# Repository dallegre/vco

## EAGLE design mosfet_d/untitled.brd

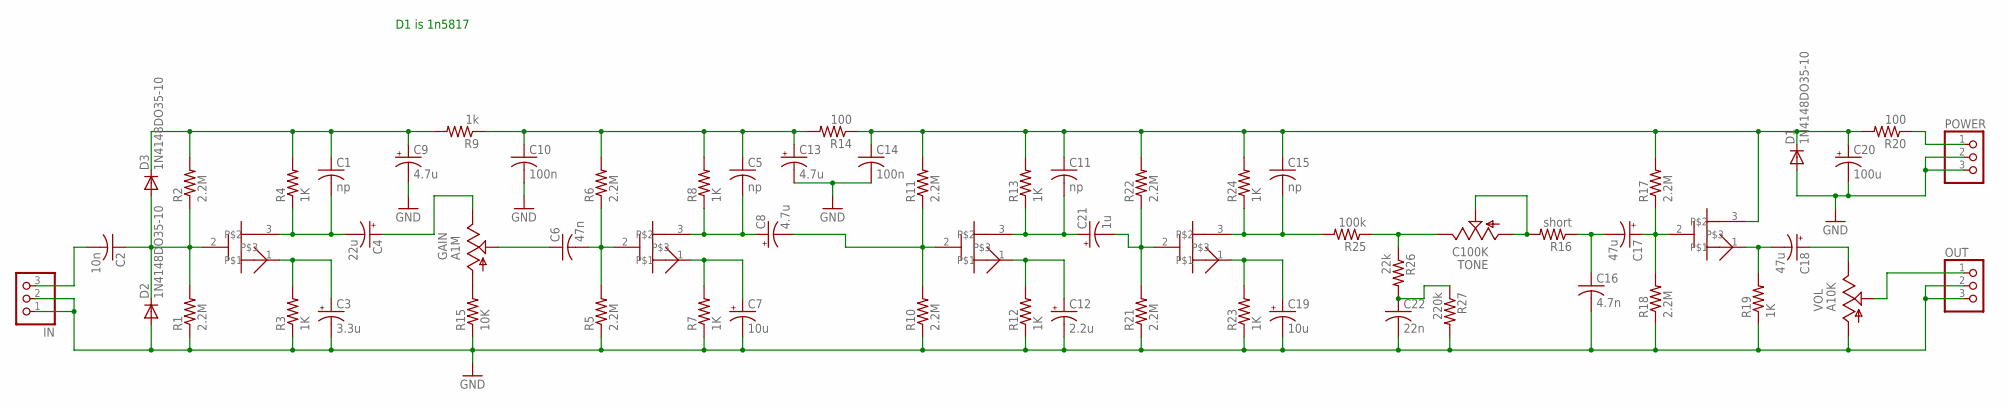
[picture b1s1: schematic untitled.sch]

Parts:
C1, C5, C11, C15: np; C050-030X075
C2: 10n; C050-030X075
C3: 3.3u; E2-5
C4: 22u; E2-5
C6: 47n; C050-030X075
C7, C19: 10u; E2-5
C8, C9, C13: 4.7u; E2-5
C10, C14: 100n; C050-030X075
C12: 2.2u; E2-5
C16: 4.7n; C050-030X075
C17, C18: 47u; E2-5
C20: 100u; E2-5
C21: 1u; E2-5
C22: 22n; C050-030X075
D1, D2, D3: 1N4148DO35-10; DO35-10
GAIN: A1M; 3RP/1610N
IN: PINHD-1X3; 1X03
OUT: PINHD-1X3; 1X03
POWER: PINHD-1X3; 1X03
R1, R2, R5, R6, R10, R11, R17, R18, R21, R22: 2.2M; 0207/7
R3, R4, R7, R8, R12, R13, R19, R23, R24: 1K; 0207/7
R9: 1k; 0207/7
R14, R20: 100; 0207/7
R15: 10K; 0207/7
R16: short; 0207/7
R25: 100k; 0207/7
R26: 22k; 0207/7
R27: 220k; 0207/7
TONE: C100K; 3RP/1610N
U$1, U$2, U$3, U$4, U$5: 2N7000_2; TO92
VOL: A10K; 3RP/1610N

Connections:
GND: C3.-, C7.-, C9.-, C10.2, C12.-, C13.-, C14.2, C16.2, C19.-, C20.-, C22.2, D1.A, D2.A, IN.1, IN.2, OUT.2, OUT.3, POWER.2, POWER.3, R1.1, R3.1, R5.1, R7.1, R10.1, R12.1, R15.1, R18.1, R19.1, R21.1, R23.1, R27.2, VOL.3 (A)
unnamed: C2.1, D2.C, D3.A, R1.2, R2.1, U$1.2
unnamed: C1.2, C4.-, R4.1, U$1.3
unnamed: C1.1, C9.+, D3.C, R2.2, R4.2, R9.2
unnamed: C4.+, GAIN.1 (E)
unnamed: C3.+, R3.2, U$1.1
unnamed: C6.2, R5.2, R6.1, U$2.2
unnamed: C5.2, C8.+, R8.1, U$2.3
unnamed: C2.2, IN.3
unnamed: C7.+, R7.2, U$2.1
unnamed: C16.1, C17.-, R16.1
unnamed: C6.1, GAIN.2 (S)
unnamed: C11.2, C21.+, R13.1, U$3.3
unnamed: C5.1, C10.1, C13.+, R6.2, R8.2, R9.1, R14.2
unnamed: C12.+, R12.2, U$3.1
unnamed: C8.-, R10.2, R11.1, U$3.2
unnamed: GAIN.3 (A), R15.2
unnamed: POWER.1, R20.1
unnamed: C17.+, R17.1, R18.2, U$4.2
unnamed: C11.1, C14.1, C15.1, C20.+, D1.C, R11.2, R13.2, R14.1, R17.2, R20.2, R22.2, R24.2, U$4.3
unnamed: R16.2, TONE.2 (S), TONE.3 (A)
unnamed: C18.-, R19.2, U$4.1
unnamed: C18.+, VOL.1 (E)
unnamed: C15.2, R24.1, R25.2, U$5.3
unnamed: OUT.1, VOL.2 (S)
unnamed: C19.+, R23.2, U$5.1
unnamed: C21.-, R21.2, R22.1, U$5.2
unnamed: C22.1, R26.2, R27.1
unnamed: R25.1, R26.1, TONE.1 (E)

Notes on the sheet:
D1 is 1n5817

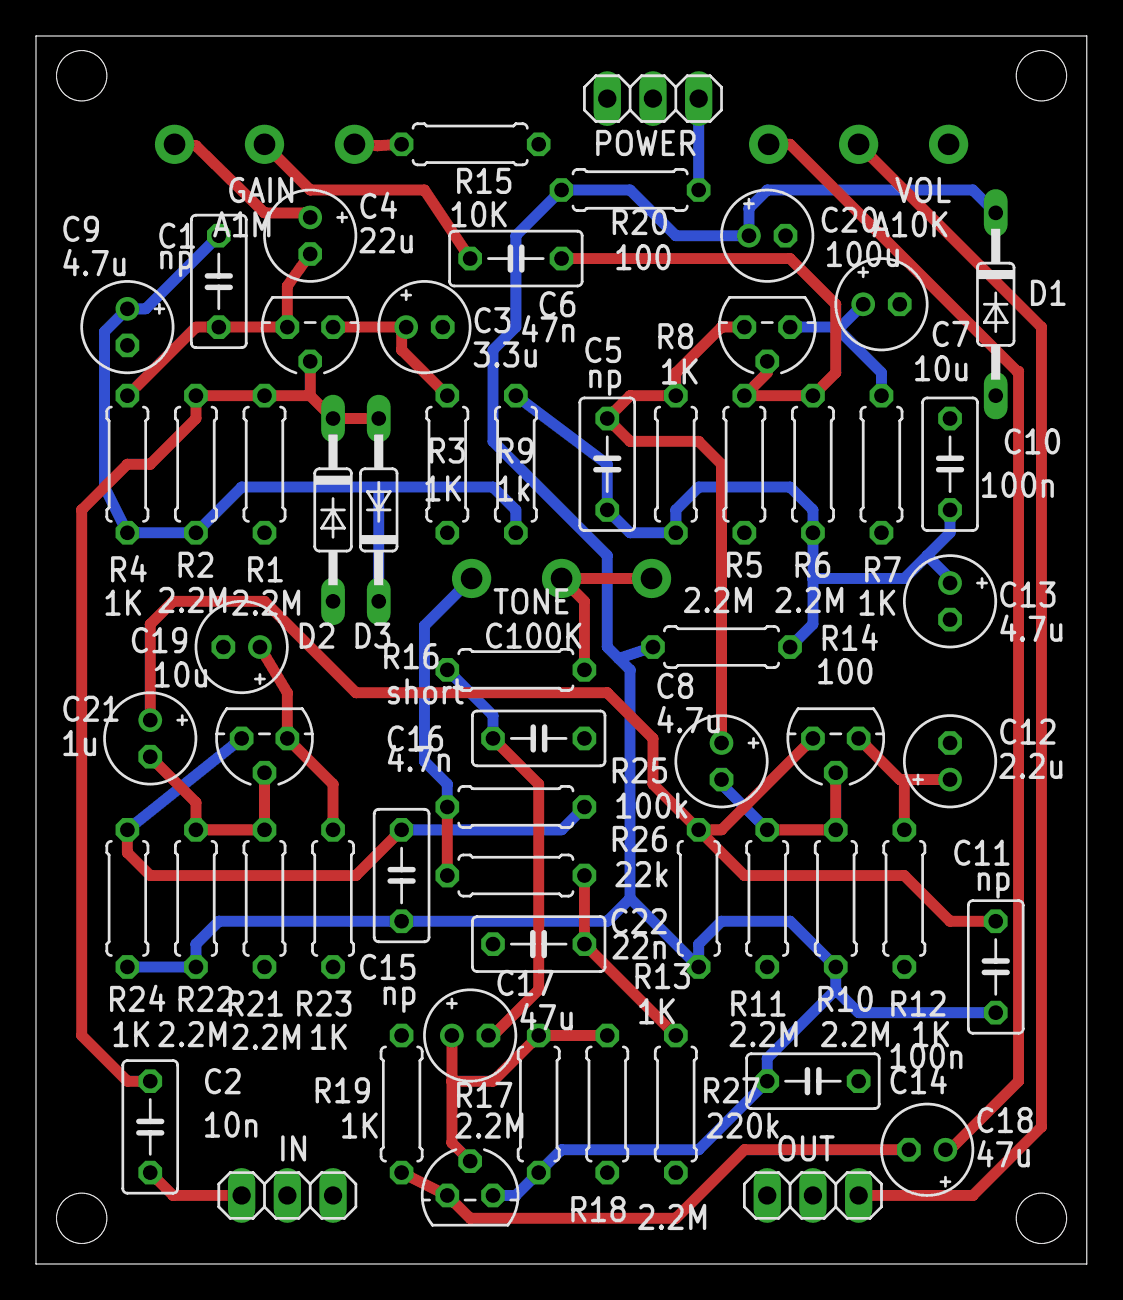
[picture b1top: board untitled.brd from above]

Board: 2 copper layers, 58.4 x 68.2 mm, 63 parts (1 on the bottom side), 29 nets.

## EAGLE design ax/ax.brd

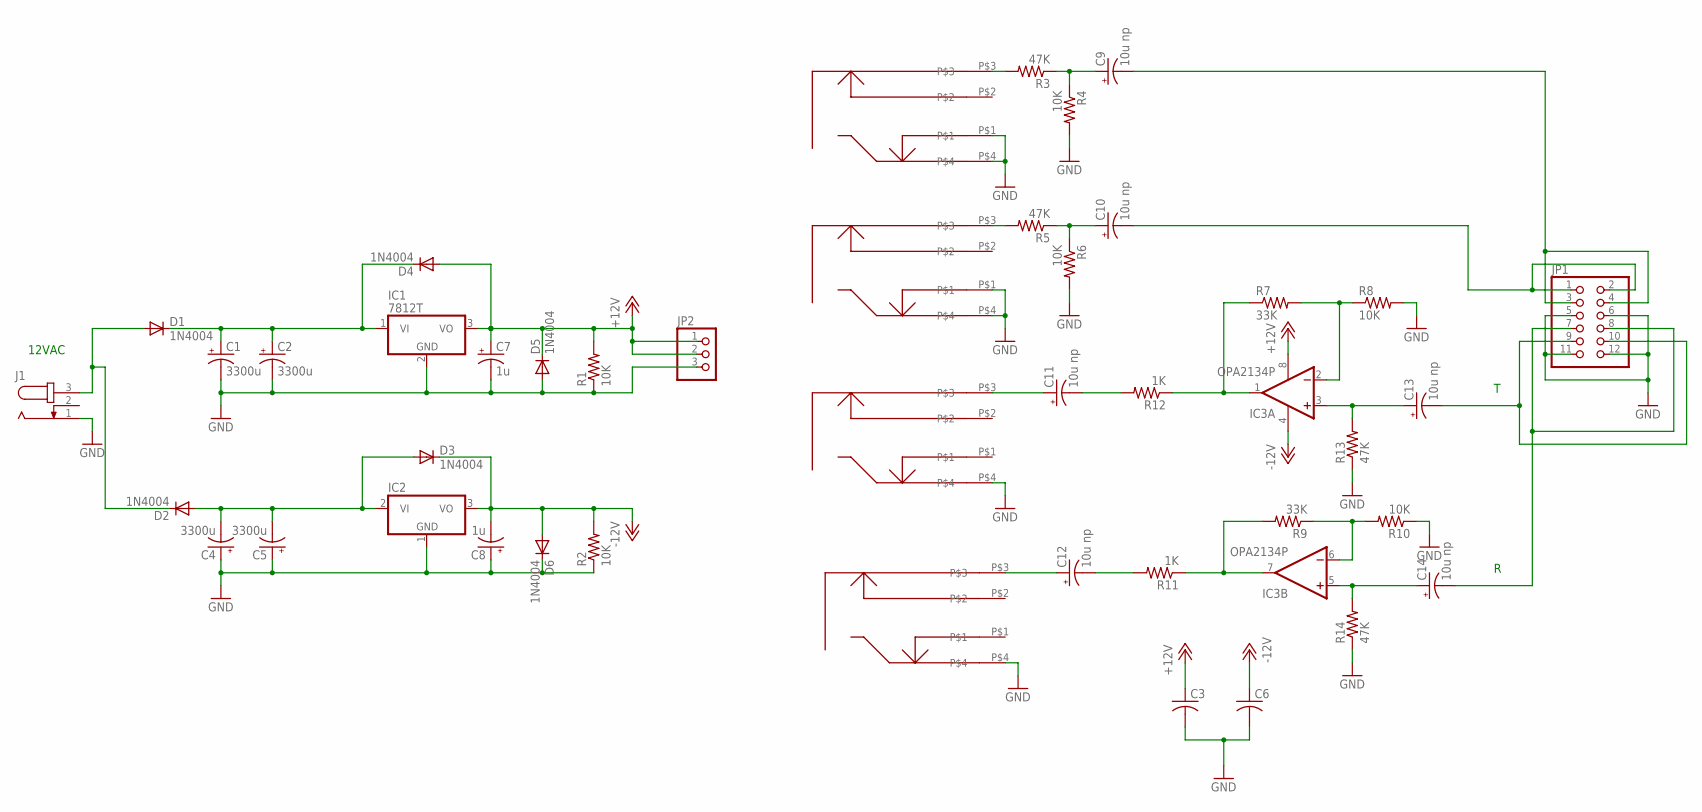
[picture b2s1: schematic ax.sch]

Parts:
C1, C2, C4, C5: 3300u; E7,5-18
C3, C6: C-US050-030X075; C050-030X075
C7, C8: 1u; E2-5
C9, C10, C11, C12, C13, C14: 10u np; E2-5
D1, D2, D3, D4, D5, D6: 1N4004; DO41-10
IC1: 7812T; TO220H
IC2: 7906T; TO220H
IC3: OPA2134P; DIL08
INL: NMJ4HCD2
INR: NMJ4HCD2
J1: JACK-PLUG0; SPC4077
JP1: PINHD-2X6; 2X06
JP2: PINHD-1X3; 1X03
OUTL: NMJ4HCD2
OUTR: NMJ4HCD2
R1, R2, R4, R6, R8, R10: 10K; 0207/7
R3, R5, R13, R14: 47K; 0207/7
R7, R9: 33K; 0207/7
R11, R12: 1K; 0207/7

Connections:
+12V: C3.1, C7.+, D4.A, D5.C, IC1.3 (VO), IC3.8 (V+), JP2.1, JP2.2, R1.2
-12V: C6.1, C8.-, D3.C, D6.A, IC2.3 (VO), IC3.4 (V-), R2.2
GND: C1.-, C2.-, C3.2, C4.+, C5.+, C6.2, C7.-, C8.+, D5.A, D6.C, IC1.2 (GND), IC2.1 (GND), INL.P$1, INL.P$4, INR.P$1, INR.P$4, J1.1, JP1.5, JP1.6, JP1.11, JP1.12, JP2.3, OUTL.P$4, OUTR.P$4, R1.1, R2.1, R4.2, R6.2, R8.2, R10.1, R13.1, R14.1
unnamed: INR.P$3, R5.2
unnamed: INL.P$3, R3.2
unnamed: C1.+, C2.+, D1.C, D4.C, IC1.1 (VI)
unnamed: C4.-, C5.-, D2.A, D3.A, IC2.2 (VI)
unnamed: C9.+, R3.1, R4.1
unnamed: C10.+, R5.1, R6.1
unnamed: C11.+, OUTL.P$3
unnamed: IC3.1 (OUT), R7.1, R12.1
unnamed: C12.+, OUTR.P$3
unnamed: IC3.7 (OUT), R9.2, R11.1
unnamed: IC3.2 (-IN), R7.2, R8.1
unnamed: IC3.6 (-IN), R9.1, R10.2
unnamed: C14.+, IC3.5 (+IN), R14.2
unnamed: C13.+, IC3.3 (+IN), R13.2
unnamed: C11.-, R12.2
unnamed: C14.-, JP1.7, JP1.8
unnamed: C13.-, JP1.9, JP1.10
unnamed: C10.-, JP1.1, JP1.2
unnamed: C12.-, R11.2
unnamed: C9.-, JP1.3, JP1.4
unnamed: D1.A, D2.C, J1.3

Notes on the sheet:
12VAC

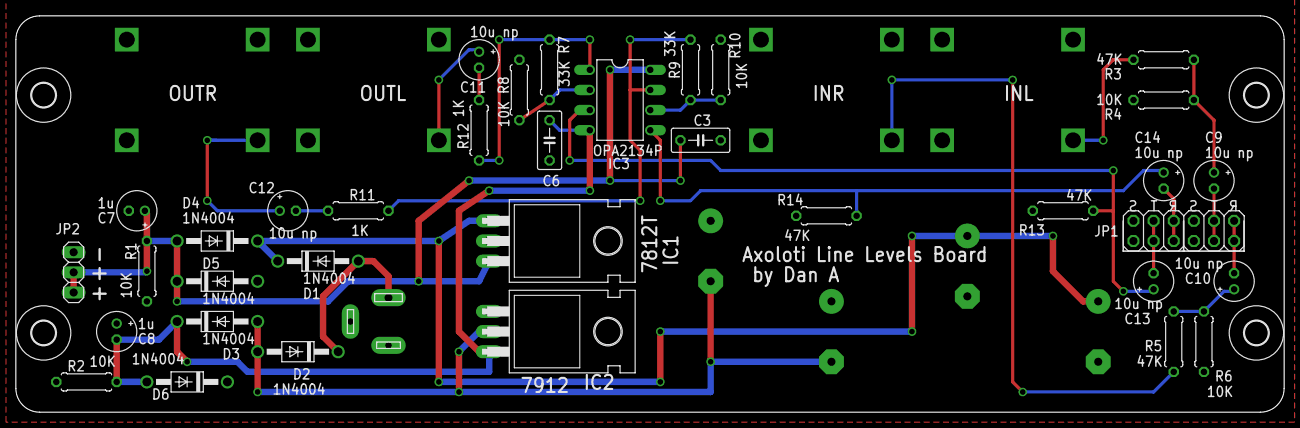
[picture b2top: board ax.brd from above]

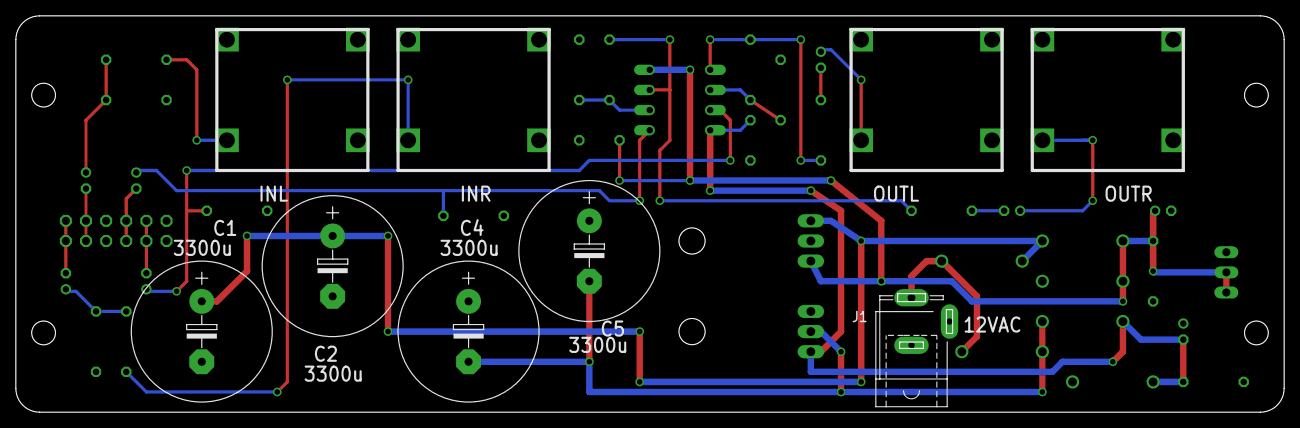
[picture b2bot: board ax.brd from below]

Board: 2 copper layers, 160.0 x 50.0 mm, 48 parts (5 on the bottom side), 24 nets.

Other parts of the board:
H1, H2, H4, H6: MOUNT-HOLE3.0; 3,0

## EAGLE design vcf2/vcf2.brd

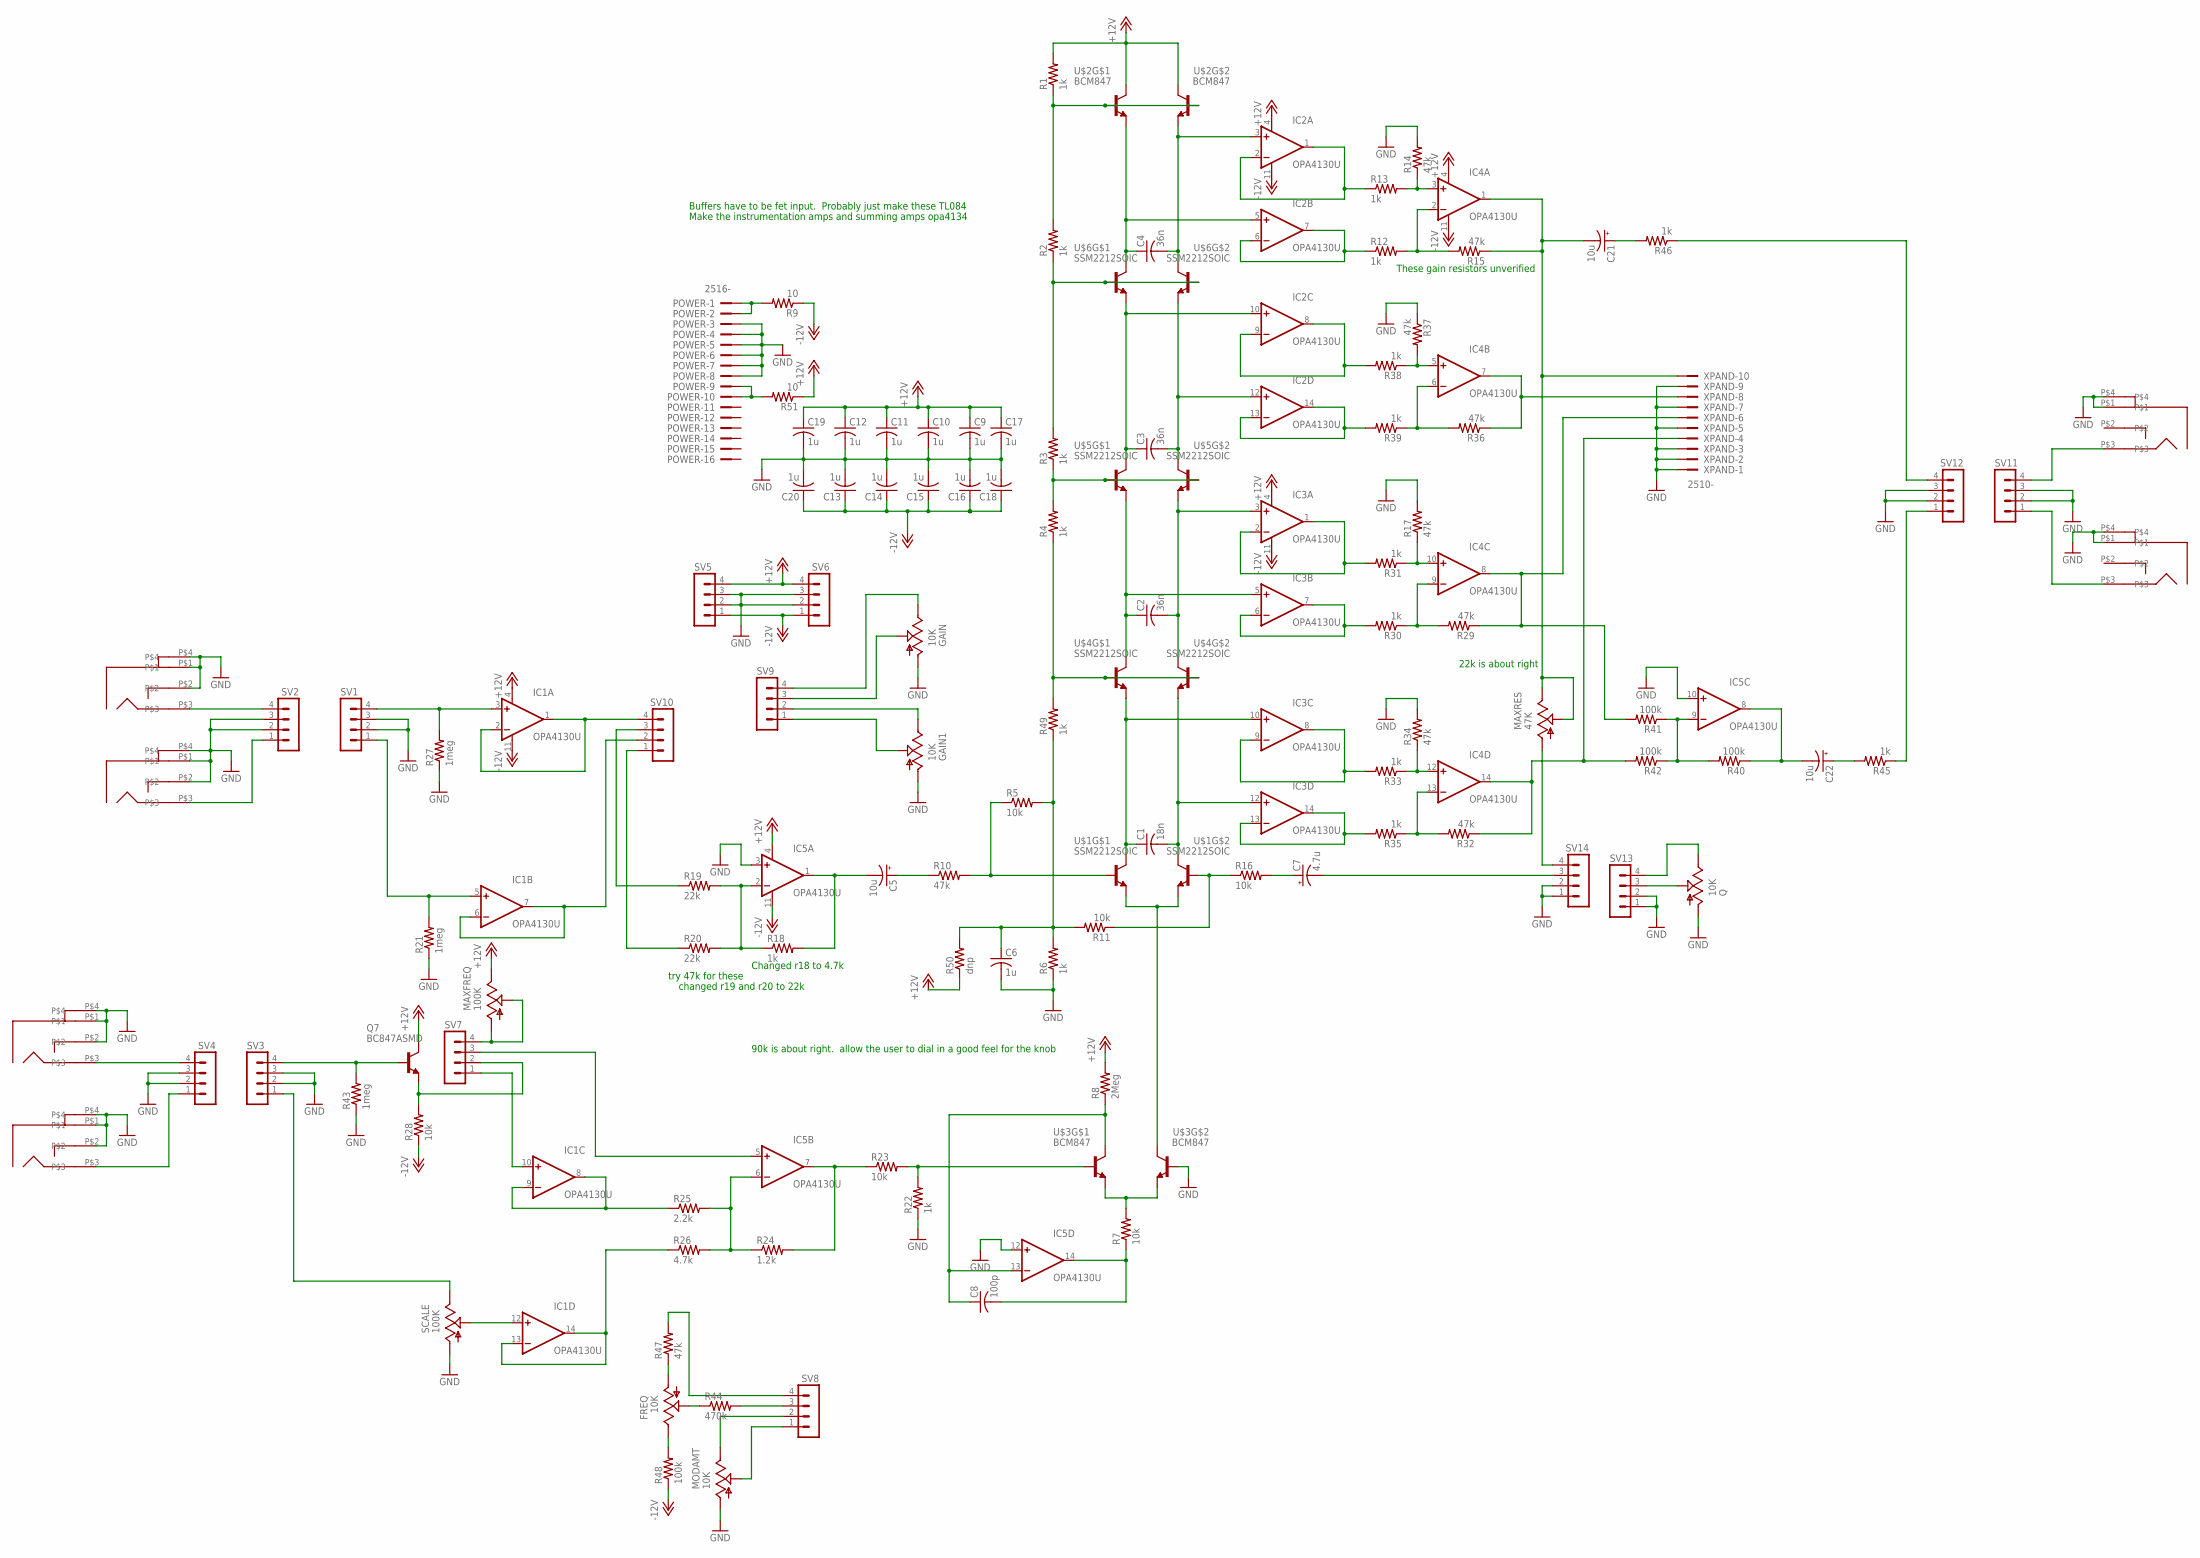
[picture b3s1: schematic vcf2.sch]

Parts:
AIN, AIN2: PJ301BM
BP: PJ301BM
C1: 18n; C0603
C2, C3, C4: 36n; C0603
C5, C21, C22: 10u; E2,5-6
C6, C9, C10, C11, C12, C13, C14, C15, C16, C17, C18, C19, C20: 1u; C0603
C7: 4.7u; E2,5-6
C8: 100p; C0603
FREQ: 10K; EVUFXJ
GAIN, GAIN1: 10K; EVUFXJ
IC1, IC2, IC3, IC4, IC5: OPA4130U; SO14
LP: PJ301BM
MAXFREQ: 100K; S64W
MAXRES: 47K; S64W
MIN: PJ301BM
MODAMT: 10K; EVUFXJ
POWER: 2516-; PAK100/2500-16
Q: 10K; EVUFXJ
Q7: BC847ASMD; SOT23
R1, R2, R3, R4, R6, R12, R13, R18, R22, R30, R31, R33, R35, R38, R39, R45, R46, R49: 1k; R0603
R5, R7, R11, R16, R23, R28: 10k; R0603
R8: 2Meg; R0603
R9, R51: 10; R0603
R10, R14, R15, R17, R29, R32, R34, R36, R37, R47: 47k; R0603
R19, R20: 22k; R0603
R21, R27, R43: 1meg; R0603
R24: 1.2k; R0603
R25: 2.2k; R0603
R26: 4.7k; R0603
R40, R41, R42, R48: 100k; R0603
R44: 470k; R0603
R50: dnp; R0603
SCALE: 100K; S64W
SV1, SV2, SV3, SV4, SV5, SV6, SV7, SV8, SV9, SV10, SV11, SV12, SV13, SV14: MA04-1
U$1, U$4, U$5, U$6: SSM2212SOIC; SO08
U$2, U$3: BCM847; SOT457R_PHILIPS
VPEROCT: PJ301BM
XPAND: 2510-; PAK100/2500-10

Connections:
+12V: C9.1, C10.1, C11.1, C12.1, C17.1, C19.1, IC1.4 (V+), IC2.4 (V+), IC3.4 (V+), IC4.4 (V+), IC5.4 (V+), MAXFREQ.E, Q7.3 (C), R1.2, R8.2, R50.1, R51.1, SV5.4, SV6.4, U$2.3 (C), U$2.6 (C)
-12V: C13.1, C14.1, C15.1, C16.1, C18.1, C20.1, IC1.11 (V-), IC2.11 (V-), IC3.11 (V-), IC4.11 (V-), IC5.11 (V-), R9.1, R28.1, R48.1, SV5.1, SV6.1
GND: AIN.P$1, AIN.P$2, AIN.P$4, AIN2.P$1, AIN2.P$2, AIN2.P$4, BP.P$1, BP.P$4, C6.2, C9.2, C10.2, C11.2, C12.2, C13.2, C14.2, C15.2, C16.2, C17.2, C18.2, C19.2, C20.2, GAIN.1 (A), GAIN1.1 (A), IC5.3 (+IN), IC5.10 (+IN), IC5.12 (+IN), LP.P$1, LP.P$4, MIN.P$1, MIN.P$2, MIN.P$4, MODAMT.1 (A), POWER.3, POWER.4, POWER.5, POWER.6, POWER.7, POWER.8, Q.1 (A), R6.1, R14.2, R17.2, R21.1, R22.1, R27.1, R34.2, R37.1, R43.1, SCALE.A, SV1.2, SV1.3, SV2.2, SV2.3, SV3.2, SV3.3, SV4.2, SV4.3, SV5.2, SV5.3, SV6.2, SV6.3, SV11.2, SV11.3, SV12.2, SV12.3, SV13.1, SV13.2, SV14.1, SV14.2, U$3.5 (B), VPEROCT.P$1, VPEROCT.P$2, VPEROCT.P$4, XPAND.1, XPAND.2, XPAND.3, XPAND.5, XPAND.7, XPAND.9
unnamed: U$1.3 (E), U$1.6 (E), U$3.3 (C)
unnamed: C1.1, IC3.10 (+IN), U$1.1 (C), U$4.3 (E)
unnamed: C2.1, IC3.5 (+IN), U$4.1 (C), U$5.3 (E)
unnamed: C3.1, IC2.10 (+IN), U$5.1 (C), U$6.3 (E)
unnamed: C3.2, IC2.12 (+IN), U$5.8 (C), U$6.6 (E)
unnamed: C2.2, IC3.3 (+IN), U$4.8 (C), U$5.6 (E)
unnamed: C1.2, IC3.12 (+IN), U$1.8 (C), U$4.6 (E)
unnamed: C4.2, IC2.3 (+IN), U$2.4 (E), U$6.8 (C)
unnamed: C4.1, IC2.5 (+IN), U$2.1 (E), U$6.1 (C)
unnamed: R1.1, R2.2, U$2.2 (B), U$2.5 (B)
unnamed: R2.1, R3.2, U$6.2 (B), U$6.7 (B)
unnamed: R3.1, R4.2, U$5.2 (B), U$5.7 (B)
unnamed: R4.1, R49.2, U$4.2 (B), U$4.7 (B)
unnamed: R5.1, R10.2, U$1.2 (B)
unnamed: IC5.2 (-IN), R18.1, R19.2, R20.2
unnamed: R7.2, U$3.1 (E), U$3.4 (E)
unnamed: C8.2, IC5.14 (OUT), R7.1
unnamed: Q7.1 (B), R43.2, SV3.4
unnamed: C8.1, IC5.13 (-IN), R8.1, U$3.6 (C)
unnamed: C5.-, IC5.1 (OUT), R18.2
unnamed: C5.+, R10.1
unnamed: R11.1, R16.1, U$1.7 (B)
unnamed: IC2.1 (OUT), IC2.2 (-IN), R13.1
unnamed: IC5.5 (+IN), SV7.3
unnamed: IC4.2 (-IN), R12.2, R15.2
unnamed: IC4.3 (+IN), R13.2, R14.1
unnamed: C21.-, IC4.1 (OUT), MAXRES.E, MAXRES.S, R15.1, XPAND.10
unnamed: IC2.8 (OUT), IC2.9 (-IN), R38.2
unnamed: IC1.8 (OUT), IC1.9 (-IN), R25.1
unnamed: IC1.6 (-IN), IC1.7 (OUT), SV10.2
unnamed: C7.+, R16.2
unnamed: MAXRES.A, SV14.4
unnamed: Q7.2 (E), R28.2, SV7.2
unnamed: R22.2, R23.2, U$3.2 (B)
unnamed: IC2.6 (-IN), IC2.7 (OUT), R12.1
unnamed: IC5.6 (-IN), R24.1, R25.2, R26.2
unnamed: IC3.1 (OUT), IC3.2 (-IN), R31.2
unnamed: IC1.13 (-IN), IC1.14 (OUT), R26.1
unnamed: IC3.8 (OUT), IC3.9 (-IN), R33.2
unnamed: SCALE.E, SV3.1
unnamed: IC1.12 (+IN), SCALE.S
unnamed: IC2.13 (-IN), IC2.14 (OUT), R39.2
unnamed: R19.1, SV10.3
unnamed: IC3.6 (-IN), IC3.7 (OUT), R30.2
unnamed: IC4.10 (+IN), R17.1, R31.1
unnamed: IC4.9 (-IN), R29.2, R30.1
unnamed: IC4.8 (OUT), R29.1, R41.2, XPAND.6
unnamed: IC3.13 (-IN), IC3.14 (OUT), R35.2
unnamed: R45.1, SV12.1
unnamed: MODAMT.2 (S), SV8.1
unnamed: IC4.13 (-IN), R32.2, R35.1
unnamed: IC4.14 (OUT), R32.1, R42.2, XPAND.4
unnamed: IC5.7 (OUT), R23.1, R24.2
unnamed: IC4.12 (+IN), R33.1, R34.1
unnamed: IC4.5 (+IN), R37.2, R38.1
unnamed: IC4.6 (-IN), R36.2, R39.1
unnamed: GAIN1.3 (E), SV9.2
unnamed: IC4.7 (OUT), R36.1, XPAND.8
unnamed: IC5.9 (-IN), R40.2, R41.1, R42.1
unnamed: FREQ.1 (A), R47.1
unnamed: C22.-, IC5.8 (OUT), R40.1
unnamed: IC1.3 (+IN), R27.2, SV1.4
unnamed: C21.+, R46.2
unnamed: R46.1, SV12.4
unnamed: FREQ.2 (S), R44.1
unnamed: FREQ.3 (E), R48.2
unnamed: IC1.1 (OUT), IC1.2 (-IN), SV10.4
unnamed: C6.1, R5.2, R6.2, R11.2, R49.1, R50.2
unnamed: IC1.5 (+IN), R21.2, SV1.1
unnamed: C22.+, R45.2
unnamed: POWER.9, POWER.10, R51.2
unnamed: POWER.1, POWER.2, R9.2
unnamed: MAXFREQ.A, MAXFREQ.S, SV7.4
unnamed: C7.-, SV14.3
unnamed: AIN.P$3, SV2.4
unnamed: AIN2.P$3, SV2.1
unnamed: MIN.P$3, SV4.4
unnamed: SV4.1, VPEROCT.P$3
unnamed: MODAMT.3 (E), SV8.2
unnamed: R44.2, SV8.3
unnamed: IC1.10 (+IN), SV7.1
unnamed: BP.P$3, SV11.1
unnamed: LP.P$3, SV11.4
unnamed: R20.1, SV10.1
unnamed: GAIN.3 (E), SV9.4
unnamed: GAIN.2 (S), SV9.3
unnamed: Q.2 (S), SV13.3
unnamed: GAIN1.2 (S), SV9.1
unnamed: Q.3 (E), SV13.4
unnamed: R47.2, SV8.4

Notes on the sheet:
Buffers have to be fet input. Probably just make these TL084
try 47k for these
These gain resistors unverified
Make the instrumentation amps and summing amps opa4134
22k is about right
90k is about right. allow the user to dial in a good feel for the knob
Changed r18 to 4.7k
changed r19 and r20 to 22k

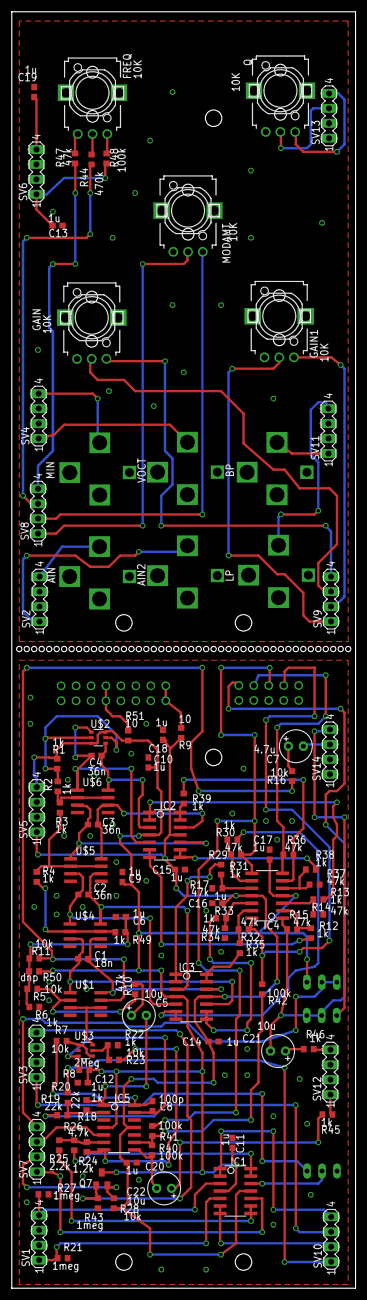
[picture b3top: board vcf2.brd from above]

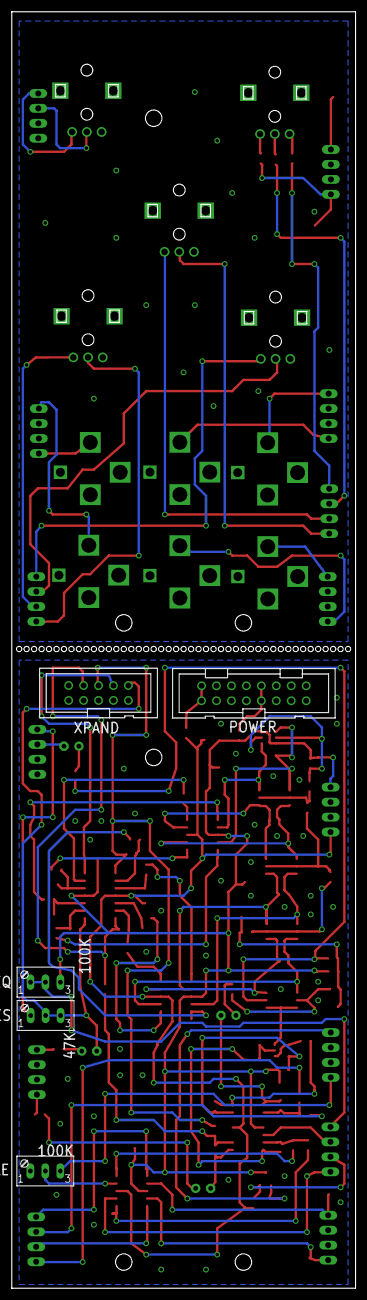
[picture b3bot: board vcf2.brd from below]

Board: 2 copper layers, 58.4 x 216.8 mm, 115 parts (5 on the bottom side), 93 nets.

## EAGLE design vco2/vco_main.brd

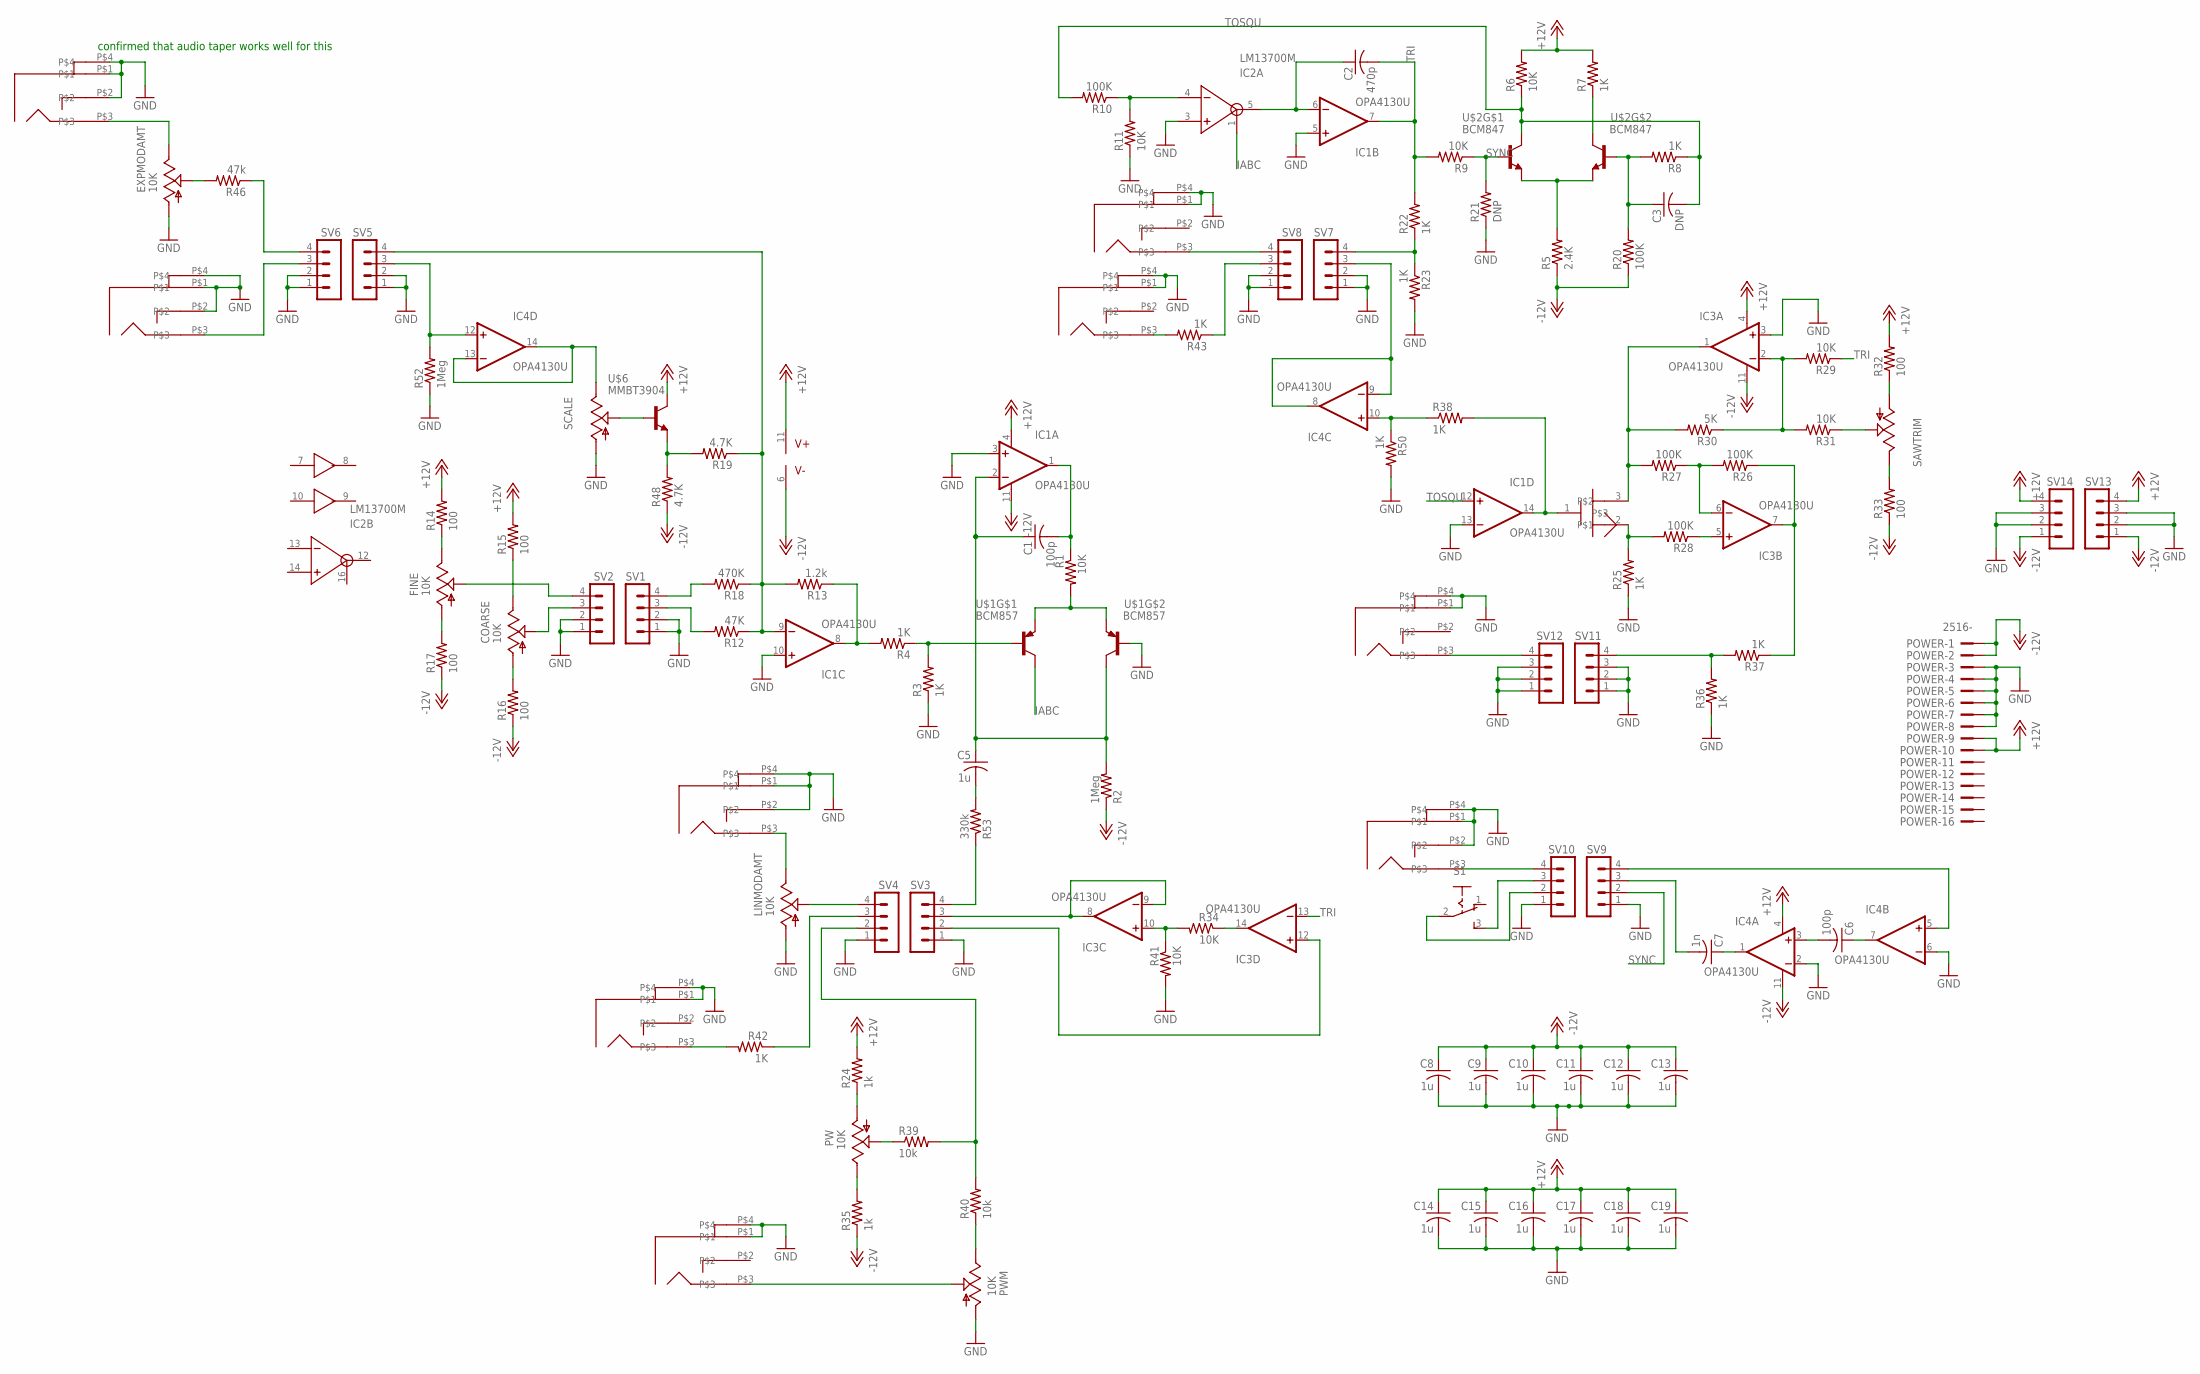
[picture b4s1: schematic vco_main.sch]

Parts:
C1, C6: 100p; C0603
C2: 470p; C0603
C3: DNP; C0603
C5, C8, C9, C10, C11, C12, C13, C14, C15, C16, C17, C18, C19: 1u; C0603
C7: 1n; C0603
COARSE: 10K; EVUFXJ
EXPMOD: PJ301BM
EXPMODAMT: 10K; EVUFXJ
FINE: 10K; EVUFXJ
IC1, IC3, IC4: OPA4130U; SO14
IC2: LM13700M; SO16
LINMOD: PJ301BM
LINMODAMT: 10K; EVUFXJ
POWER: 2516-; PAK100/2500-16
PW: 10K; EVUFXJ
PWIN: PJ301BM
PWM: 10K; EVUFXJ
PWOUT: PJ301BM
R1, R6, R9, R11, R29, R31, R34, R41: 10K; R0603
R2, R52: 1Meg; R0603
R3, R4, R7, R8, R22, R23, R25, R36, R37, R38, R42, R43, R50: 1K; R0603
R5: 2.4K; R0603
R10, R20, R26, R27, R28: 100K; R0603
R12: 47K; R0603
R13: 1.2k; R0603
R14, R15, R16, R17, R32, R33: 100; R0603
R18: 470K; R0603
R19, R48: 4.7K; R0603
R21: DNP; R0603
R24, R35: 1k; R0603
R30: 5K; R0603
R39, R40: 10k; R0603
R46: 47k; R0603
R53: 330k; R0603
S1: 255SB
SAW: PJ301BM
SAWTRIM: TRIM_US-B64Y; B64Y
SCALE: TRIM_US-B64Y; B64Y
SQUARE: PJ301BM
SV1, SV2, SV3, SV4, SV5, SV6, SV7, SV8, SV9, SV10, SV11, SV12, SV13, SV14: MA04-1
SYNC: PJ301BM
TRIOUT: PJ301BM
U$1: BCM857; SOT457R_PHILIPS
U$2: BCM847; SOT457R_PHILIPS
U$3: 2N7000; SOT23
U$6: MMBT3904; SOT23
VPEROCT: PJ301BM

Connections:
+12V: C14.1, C15.1, C16.1, C17.1, C18.1, C19.1, IC1.4 (V+), IC2.11 (V+), IC3.4 (V+), IC4.4 (V+), POWER.9, POWER.10, R6.2, R7.2, R14.2, R15.2, R24.2, R32.2, SV13.4, SV14.4, U$6.3 (C)
-12V: C8.1, C9.1, C10.1, C11.1, C12.1, C13.1, IC1.11 (V-), IC2.6 (V-), IC3.11 (V-), IC4.11 (V-), POWER.1, POWER.2, R2.1, R5.1, R16.1, R17.1, R20.1, R33.1, R35.1, R48.1, SV13.1, SV14.1
GND: C8.2, C9.2, C10.2, C11.2, C12.2, C13.2, C14.2, C15.2, C16.2, C17.2, C18.2, C19.2, EXPMOD.P$1, EXPMOD.P$2, EXPMOD.P$4, EXPMODAMT.1 (A), IC1.3 (+IN), IC1.5 (+IN), IC1.10 (+IN), IC1.13 (-IN), IC2.3 (+IN), IC3.3 (+IN), IC4.2 (-IN), IC4.6 (-IN), LINMOD.P$1, LINMOD.P$2, LINMOD.P$4, LINMODAMT.1 (A), POWER.3, POWER.4, POWER.5, POWER.6, POWER.7, POWER.8, PWIN.P$1, PWIN.P$4, PWM.1 (A), PWOUT.P$1, PWOUT.P$4, R3.1, R11.1, R21.1, R23.2, R25.1, R36.1, R41.2, R50.2, R52.1, SAW.P$1, SAW.P$4, SCALE.A, SQUARE.P$1, SQUARE.P$4, SV1.1, SV1.2, SV2.1, SV2.2, SV3.1, SV4.1, SV5.1, SV5.2, SV6.1, SV6.2, SV7.1, SV7.2, SV8.1, SV8.2, SV9.1, SV10.1, SV11.1, SV11.2, SV11.3, SV12.1, SV12.2, SV12.3, SV13.2, SV13.3, SV14.2, SV14.3, SYNC.P$1, SYNC.P$2, SYNC.P$4, TRIOUT.P$1, TRIOUT.P$4, U$1.5 (B), VPEROCT.P$1, VPEROCT.P$2, VPEROCT.P$4
IABC: IC2.1 (IABC), U$1.6 (C)
unnamed: IC3.14 (OUT), R34.1
unnamed: C1.2, IC1.1 (OUT), R1.1
unnamed: C1.1, C5.1, IC1.2 (-IN), R2.2, U$1.3 (C)
unnamed: C3.1, R8.2, R20.2, U$2.5 (B)
unnamed: IC1.9 (-IN), R12.1, R13.2, R18.1, R19.1, SV5.4
unnamed: C6.2, IC4.3 (+IN)
unnamed: R3.2, R4.1, U$1.2 (B)
unnamed: FINE.3 (E), R14.1
unnamed: IC4.10 (+IN), R38.1, R50.1
unnamed: R25.2, R28.2, U$3.2
unnamed: R5.2, U$2.1 (E), U$2.4 (E)
unnamed: R1.2, U$1.1 (E), U$1.4 (E)
unnamed: R22.1, R23.1, SV7.4
unnamed: IC2.4 (-IN), R10.1, R11.2
unnamed: IC1.8 (OUT), R4.2, R13.1
unnamed: COARSE.3 (E), R15.1
unnamed: COARSE.1 (A), R16.2
unnamed: COARSE.2 (S), SV2.3
unnamed: C2.1, IC1.6 (-IN), IC2.5 (OUT)
unnamed: FINE.1 (A), R17.2
unnamed: FINE.2 (S), SV2.4
unnamed: R19.2, R48.2, U$6.2 (E)
unnamed: R7.1, U$2.3 (C)
unnamed: LINMOD.P$3, LINMODAMT.3 (E)
unnamed: IC3.5 (+IN), R28.1
unnamed: IC3.6 (-IN), R26.2, R27.1
unnamed: IC3.7 (OUT), R26.1, R37.1
unnamed: IC3.1 (OUT), R27.2, R30.2, U$3.3
unnamed: R32.1, SAWTRIM.A
unnamed: IC3.2 (-IN), R29.2, R30.1, R31.2
unnamed: R33.2, SAWTRIM.E
unnamed: R31.1, SAWTRIM.S
unnamed: PWOUT.P$3, R42.2
unnamed: IC3.10 (+IN), R34.2, R41.1
unnamed: R43.2, SQUARE.P$3
unnamed: IC3.8 (OUT), IC3.9 (-IN), SV3.3
unnamed: R36.2, R37.2, SV11.4
unnamed: R39.2, R40.2, SV4.2
unnamed: PW.2 (S), R39.1
unnamed: IC4.8 (OUT), IC4.9 (-IN), SV7.3
unnamed: PW.1 (A), R24.1
unnamed: EXPMODAMT.2 (S), R46.2
unnamed: PW.3 (E), R35.2
unnamed: PWM.3 (E), R40.1
unnamed: EXPMOD.P$3, EXPMODAMT.3 (E)
unnamed: R53.1, SV3.4
unnamed: C6.1, IC4.7 (OUT)
unnamed: C5.2, R53.2
unnamed: C7.1, IC4.1 (OUT)
unnamed: SV10.4, SYNC.P$3
unnamed: C7.2, SV9.3
unnamed: SAW.P$3, SV12.4
unnamed: R18.2, SV1.4
unnamed: IC4.12 (+IN), R52.2, SV5.3
unnamed: IC4.13 (-IN), IC4.14 (OUT), SCALE.E
unnamed: SCALE.S, U$6.1 (B)
unnamed: IC1.14 (OUT), R38.2, U$3.1
unnamed: R12.2, SV1.3
unnamed: LINMODAMT.2 (S), SV4.4
unnamed: R42.1, SV4.3
unnamed: R46.1, SV6.4
unnamed: SV6.3, VPEROCT.P$3
unnamed: SV8.4, TRIOUT.P$3
unnamed: R43.1, SV8.3
unnamed: IC4.5 (+IN), SV9.4
unnamed: S1.3 (S), SV10.3
unnamed: S1.2, SV10.2
unnamed: IC3.12 (+IN), SV3.2
unnamed: PWIN.P$3, PWM.2 (S)
SYNC: R9.1, R21.2, SV9.2, U$2.2 (B)
TOSQU: C3.2, IC1.12 (+IN), R6.1, R8.1, R10.2, U$2.6 (C)
TRI: C2.2, IC1.7 (OUT), IC3.13 (-IN), R9.2, R22.2, R29.1

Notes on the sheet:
confirmed that audio taper works well for this

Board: 2 copper layers, 107 parts (3 on the bottom side), 76 nets, no tracks yet.

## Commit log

2015-10-24 added gerbers
2015-10-25 fixed the schematic. need to check polarity on current source and square comparator. moved most of the labels to the silkscreen layer, but need to do that with the new components.
2015-10-25 fixed schematic. moved all labels to silkscreen. fixed layout. need to make gerbers.
2015-10-25 fixed some drc errors. made gerbers. silkscreen gerber doesn't seem to be getting the fonts correctly.
2015-10-28 fixed silkscreen. fixed linear mod. started to think about critical nets.
2015-11-03 fixed up the symmetry. added a front panel.
2015-11-03 actually added the panel.
2015-11-03 added some to do notes to the schematic for final checking.
2015-11-04 fixed a serious problem with the saw. cleaned some nets up.
2015-11-04 cleaned up the layout a bit. fixed component values.
2015-11-04 did some stuff
2015-11-06 fixed some stuff
2015-11-06 made some major layout changes.
2015-11-06 made major layout changes
2015-11-07 flipped the pnp pair right side up in schematic.
2015-11-07 added a vcf schematic
2015-11-08 lasdkfj
2015-11-08 pretty much finished the vcf schematic. started vcf layout
2015-11-08 made changes to the vcf board
2015-11-08 changed layouts, changed vias to round.
2015-11-09 added fancy graphics to vco. about ready to tape out.
2015-11-14 got the boards! adding notes on component changes to schematic.
2015-11-14 added some more notes
2015-11-14 improved notes
2015-11-14 fixed most of the silkscreen issues.
2015-11-15 pretty much finished the front panel. the led and switch holes may need review
2015-11-16 finished er up. ordered 2nd rev of pcb and 1st rev of front panel.
2015-11-16 added open hardware logo. added all bmps to repository.
2015-11-24 made some small changes that drove me crazy during assembly.
2015-12-05 changed a bunch of stuff.
2016-02-20 almost done with the filter board
2016-02-25 vcf, added protection and input resistors. Added holes on corners. fixed silkscreen. generated viable gerbers for vcf.
2016-02-26 added some critical stuff. sent the board to pcbway for checking.
2016-02-26 fixed polarity on resonance pot. Sent out to fab.
2016-02-28 added a schematic for the envelope. power needs to be hooked up for the switch and gates
2016-03-05 made some of the post first draft schematic changes
2016-03-06 made bug fixes. almost ready to send out again.
2016-03-07 fixed the input impedance situation.
2016-03-07 moved the tempco to next to the exponentiator pair
2016-03-07 sent out the vcf board for 2nd revision
2016-03-09 worked on the env some more
2016-03-09 added ota
2016-03-10 more work on the env.
2016-03-10 almost done with the env. need to check things (pot polarity)
2016-03-11 fixed values in schematic after getting 2nd board rev back.
2016-03-25 added a vca. made changes to the filter components
2016-03-26 almost got the vca pcb done
2016-06-10 fixed bugs in vca. did more changing of vcf components. need to route a trace in vcf
2016-06-24 made changes to vca after fab. about ready to send 2nd rev of vcf in.
2016-07-27 added notes in schem about reducing input attenuation resistors
2016-07-29 added leds to env
2016-07-29 did drc check for env
2016-08-21 did some post fab changes to env
2016-08-21 made changes to env to send out again. need to fix bi color led.
2016-08-21 got the 2nd set of gerbers for env ready to send out
2016-08-22 fixed the logic supply for the switch in the env
2016-09-01 Added env front panel. Fixed a resistor in the env.
2017-01-04 fixed the env front panel and sent it out
2017-05-20 changed the vca to be a 2 board design with a mixer for the input.q
2017-05-20 finished the vca. more or less ready.
2017-05-23 finished vca. probably needs a series protection resistor on output.
2017-05-27 made a couple post fab vca changes
2017-05-28 added 2 board rev of the vcf in a separate folder
2017-05-31 vcf2 changes
2017-06-01 almost finished vcf2 and vca 2nd rev. Need to verify mechanical dimensions
2017-06-03 confirmed mechanicals on vcf2
2017-06-03 added a musical keyboard sequencer idea with cherry switches
2017-06-07 made gerbers for vcf2
2017-06-07 added keyboard_simple. it's a more practical scaled down keyboard thing
2017-06-09 sent out vca again
2017-06-10 added a 2 layer version of the vco
2017-06-10 more work on vco2
2017-06-28 progress..
2017-10-07 added some stuff to the library
2019-02-17 added axoloti board and mosfet distortion
2019-03-22 fixed pinout of transistors in mosfet d
2019-03-23 fixed component values in mosfet d
2019-04-03 added pcb mounted pots to distortion
2019-04-04 redesigned the distortion pcb
